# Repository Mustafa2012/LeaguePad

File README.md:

# LeaguePad

A macropad I made to play LEAGUE OF LEGENDS! It has 12 keys and an oled display! This is the first pcb I have ever made !

## Features!
- A big 0.91" OLED screen
- Cool case
- 12x MX-Style switches
- kmk firmware!
- custom pcb

## PCB
I designed the pcb using Kicad!
Here are pictures of my pcb:

| **Schematic and PCB** | 
|---------------|

## CAD
Designed using Onshape! Everything fits together with 4 m3 screws and bolts

## Firmware

I wrote the firmware using kmk, you can see it inside the repo. It can be used to play LEAGUE OF LEGENDS

## BOM
- 1 SEEEDUINO XIAO RP2040
- 12x  MX-STYLE Switches 
- 12x 1N4148 diodes
- 1x SSD1306 128x32p LED  (GND-VCC-SCL-SDA)
- 4x same screws as orpheuspad and corresponding nuts

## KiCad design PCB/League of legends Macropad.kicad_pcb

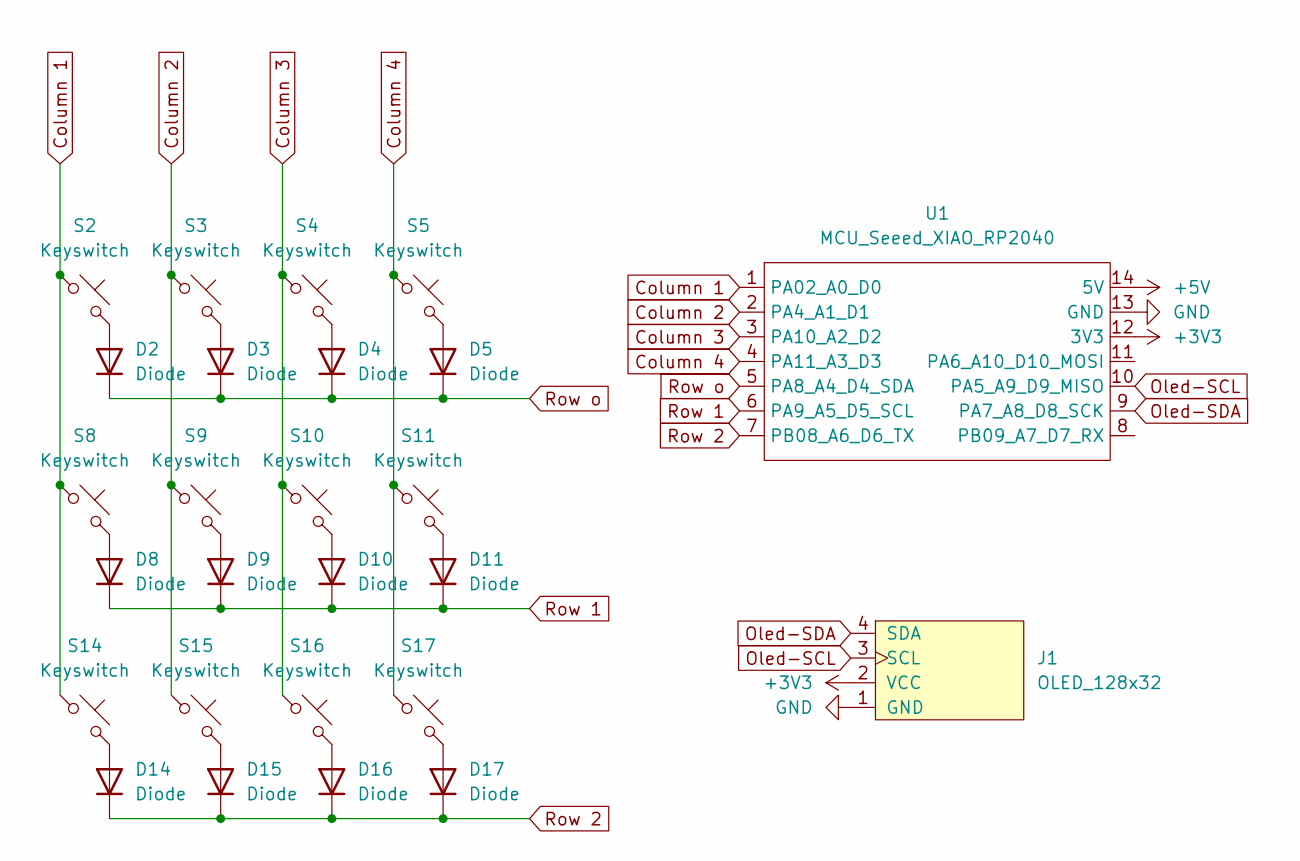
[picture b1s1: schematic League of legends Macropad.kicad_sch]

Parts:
D2, D3, D4, D5, D8, D9, D10, D11, D14, D15, D16, D17: Diode; Diode_DO-35
J1: OLED_128x32
S2, S3, S4, S5, S8, S9, S10, S11, S14, S15, S16, S17: Keyswitch; MX_PCB_1.00u
U1: MCU_Seeed_XIAO_RP2040; Seeed_XIAO_RP2040

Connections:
+3V3: J1.2 (VCC), U1.12 (3V3)
+5V: U1.14 (5V)
Column 1: S2.1, S8.1, S14.1, U1.1 (PA02_A0_D0)
Column 2: S3.1, S9.1, S15.1, U1.2 (PA4_A1_D1)
Column 3: S4.1, S10.1, S16.1, U1.3 (PA10_A2_D2)
Column 4: S5.1, S11.1, S17.1, U1.4 (PA11_A3_D3)
GND: J1.1 (GND), U1.13 (GND)
unnamed: D2.2 (A), S2.2
unnamed: D3.2 (A), S3.2
unnamed: D4.2 (A), S4.2
unnamed: D5.2 (A), S5.2
unnamed: D8.2 (A), S8.2
unnamed: D9.2 (A), S9.2
unnamed: D10.2 (A), S10.2
unnamed: D11.2 (A), S11.2
unnamed: D14.2 (A), S14.2
unnamed: D15.2 (A), S15.2
unnamed: D16.2 (A), S16.2
unnamed: D17.2 (A), S17.2
Oled-SCL: J1.3 (SCL), U1.10 (PA5_A9_D9_MISO)
Oled-SDA: J1.4 (SDA), U1.9 (PA7_A8_D8_SCK)
Row 1: D8.1 (K), D9.1 (K), D10.1 (K), D11.1 (K), U1.6 (PA9_A5_D5_SCL)
Row 2: D14.1 (K), D15.1 (K), D16.1 (K), D17.1 (K), U1.7 (PB08_A6_D6_TX)
Row o: D2.1 (K), D3.1 (K), D4.1 (K), D5.1 (K), U1.5 (PA8_A4_D4_SDA)

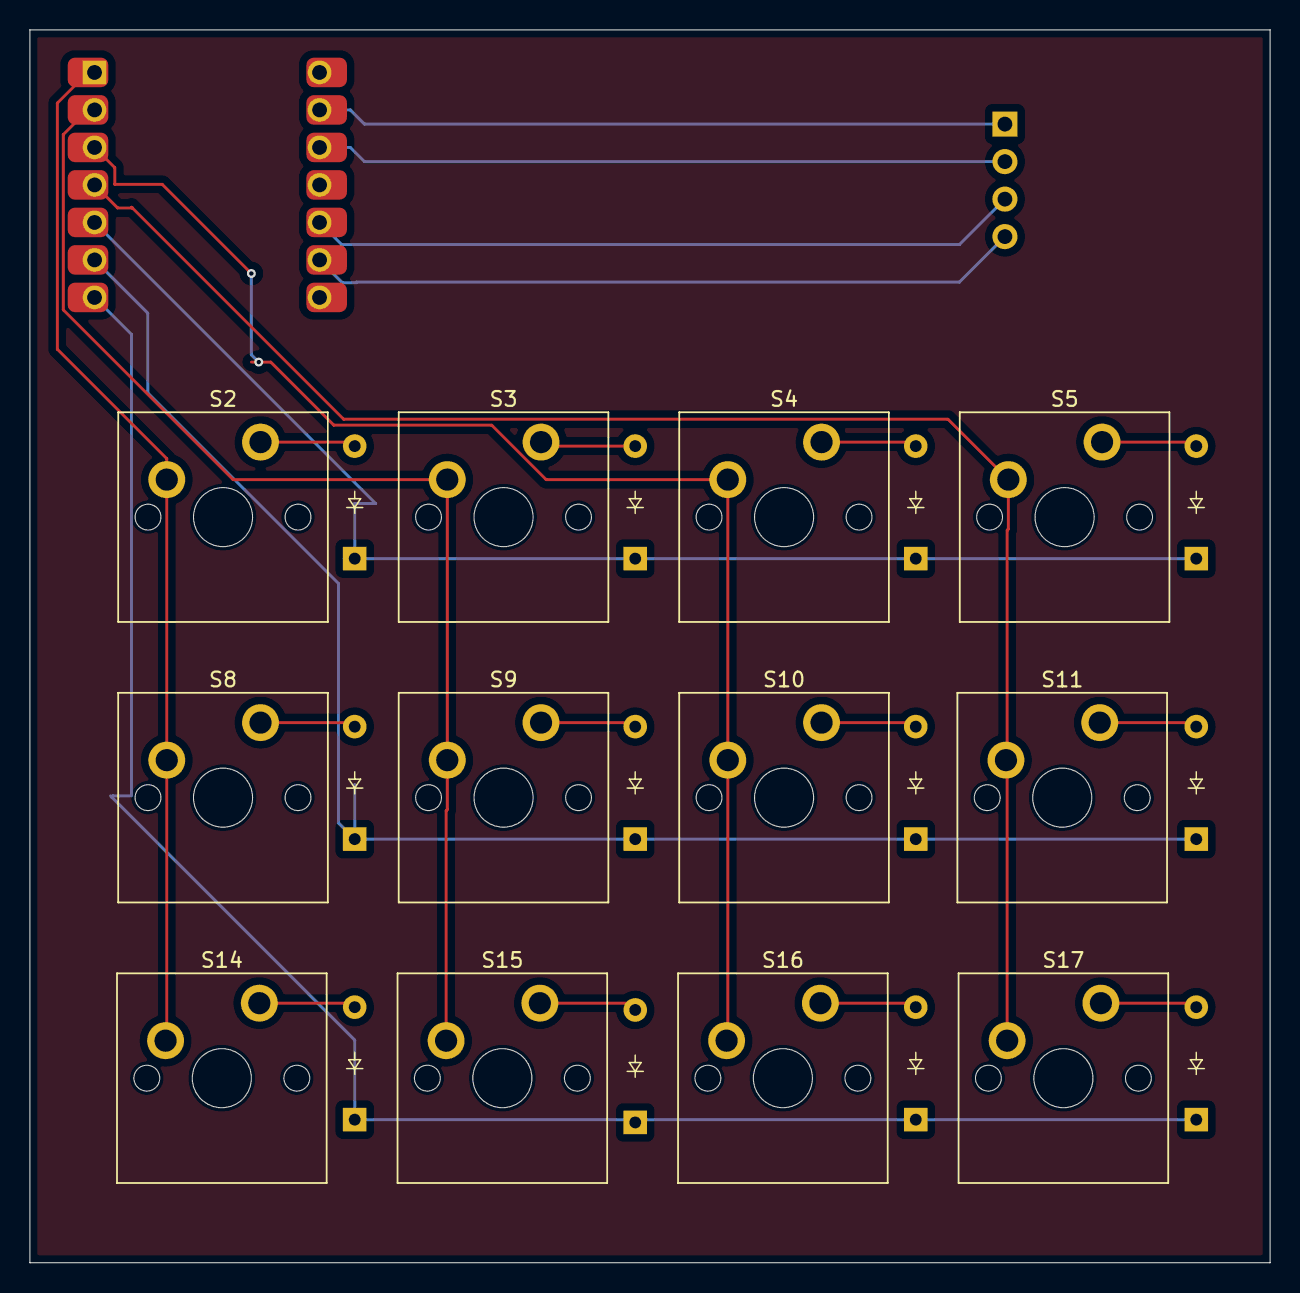
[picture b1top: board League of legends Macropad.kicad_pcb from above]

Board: 2 copper layers, 84.0 x 83.5 mm, 26 parts (0 on the bottom side), 23 nets.

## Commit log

2025-07-31 Project
2025-07-31 Delete
2025-07-31 Production
